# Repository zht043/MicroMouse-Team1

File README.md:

# MicroMouse-Team1

************************************************************************************************************************************

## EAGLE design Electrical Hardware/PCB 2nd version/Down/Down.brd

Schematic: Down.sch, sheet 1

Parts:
C1, C2: 12pF; 0603
CEM1, CEM3, CEM5, CEM7: 4.7µF; 0805
CEM2, CEM4, CEM6, CEM8: 0.1µF; 0805
CLMC_1: 0.1µF; 0805
CLMC_2: 100uF; EIA7343
CPWR_1, CPWR_5: 0.47µF; 0805
CPWR_2, CPWR_6: 22uF or 33uF; 0805
CPWR_3: 0.1uF; 0805
CPWR_4: 0.33µF; 0805
CRMC_1: 0.1µF; 0805
CRMC_2: 100uF; EIA7343
C_BAT: 2.2uF; 0805
C_V1, C_V2, C_V3, C_V4: 0.1uF; 0805
C_VA1: 2.2uF; 0805
C_VA2: 0.1uF; 0805
C_VCAP1, C_VCAP2: 2.2uF; 0805
IREL: JST-PH2
IRELF: JST-PH2
IRER: JST-PH2
IRERF: JST-PH2
IRRL: JST-PH2
IRRLF: JST-PH2
IRRR: JST-PH2
IRRRF: JST-PH2
LED1, LED2, LED3, LED4: BLUE; LED-1206
LEDR1, LEDR2, LEDR3, LEDR4: 1k; 0805
LEFTMOTOR: PINHD-2X3; 2X03
LM: 1X4
P1: JST-PH2
REG1, REG3: LM2940IMP-5.0/NOPB; MP04A
REG2: LM2937IMP-3.3/NOPB; MP04A
RIGHTMOTOR: PINHD-2X3; 2X03
RM: 1X4
RRE1, RRE2, RRE3, RRE4, RRE5, RRE6: 1.8k; 0805
R_EM, R_EM2, R_EM4, R_EM6: 5ohm; 0805
R_EM1, R_EM3, R_EM5, R_EM7: 10k; 0805
R_LMC_1, R_LMC_2: 47K; 0805
R_RMC_1, R_RMC_2: 47k; 0805
R_VMTR_1: 10K; 0805
R_VMTR_2: 20K; 0805
SPI2: 1X4
SWD: 1X5
U$1: STM32F405/415_LQFP64
U$2: OSC
U$3: 1X3
U$4, U$5, U$6, U$7: MCH3474
U$8, U$9: 1X2
U$15, U$17: TC4427(8MSOP)
U$16, U$18: ZXMHC3F381N8

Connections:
3.3V: CPWR_4.1, C_BAT.2, C_V1.2, C_V2.1, C_V3.2, C_V4.2, C_VA1.2, C_VA2.2, REG2.3 (OUT), SWD.5, U$1.VBAT, U$1.VDDA, U$1.VDD_0, U$1.VDD_1, U$1.VDD_2, U$1.VDD_3, U$3.2
5V: CPWR_3.1, CPWR_6.1, LEFTMOTOR.4, REG2.1 (IN), REG3.3 (VOUT), RIGHTMOTOR.4
A5V: CEM1.2, CEM2.1, CEM3.2, CEM4.1, CEM5.2, CEM6.1, CEM7.2, CEM8.1, CPWR_2.1, IREL.2, IRELF.2, IRER.2, IRERF.2, IRRL.2, IRRR.2, LEDR1.2, LEDR2.2, LEDR3.2, LEDR4.2, REG1.3 (VOUT)
AGND: CEM1.1, CEM2.2, CEM3.1, CEM4.2, CEM5.1, CEM6.2, CEM7.1, CEM8.2, CPWR_1.2, CPWR_2.2, LED1.C, LED2.C, LED3.C, LED4.C, REG1.2 (GND_2), REG1.4 (GND), RRE1.1, RRE2.1, RRE3.1, RRE4.1, RRE5.1, RRE6.1, R_EM1.1, R_EM3.1, R_EM5.1, R_EM7.1, R_VMTR_1.1, U$3.3, U$4.S, U$5.S, U$6.S, U$7.S
EMD_L: IREL.1, R_EM4.2
EMD_LF: IRELF.1, R_EM.2
EMD_R: IRER.1, R_EM6.2
EMD_RF: IRERF.1, R_EM2.2
EM_L: R_EM5.2, U$1.PA8, U$4.G
EM_LF: R_EM1.2, U$1.PA10, U$5.G
EM_R: R_EM7.2, U$1.PA9, U$7.G
EM_RF: R_EM3.2, U$1.PA11, U$6.G
GND: C1.2, C2.2, CPWR_3.2, CPWR_4.2, CPWR_5.2, CPWR_6.2, C_BAT.1, C_V1.1, C_V2.2, C_V3.1, C_V4.1, C_VA1.1, C_VA2.1, C_VCAP1.1, C_VCAP2.2, REG2.2 (GND), REG3.2 (GND_2), REG3.4 (GND), SWD.3, U$1.BOOT0, U$1.PB2, U$1.VSSA, U$1.VSS_0, U$1.VSS_1, U$3.1
L: LEFTMOTOR.1, U$16.N1D/P1D
LENCA: LEFTMOTOR.6, LM.1
LENCB: LEFTMOTOR.5, LM.2
LPWMA: LM.4, R_LMC_1.2, U$15.IN_A
LPWMB: LM.3, R_LMC_2.2, U$15.IN_B
MGND: CLMC_1.1, CLMC_2.C (-), CRMC_1.1, CRMC_2.C (-), LEFTMOTOR.3, P1.2, RIGHTMOTOR.3, R_LMC_1.1, R_LMC_2.1, R_RMC_1.1, R_RMC_2.1, U$15.GND, U$16.N1S/N2S, U$17.GND, U$18.N1S/N2S
unnamed: R_EM.1, U$5.D
unnamed: R_EM2.1, U$6.D
unnamed: R_EM4.1, U$4.D
unnamed: R_EM6.1, U$7.D
unnamed: LED2.A, LEDR1.1
unnamed: LED3.A, LEDR2.1
unnamed: LED4.A, LEDR3.1
unnamed: LED1.A, LEDR4.1
unnamed: LEFTMOTOR.2, U$16.N2D/P2D
unnamed: RIGHTMOTOR.1, U$18.N2D/P2D
OSC_IN: C1.1, U$1.PH0, U$2.P$2 (IN2)
OSC_OUT: C2.1, U$1.PH1, U$2.P$1 (IN1)
OUTA: U$17.OUT_A, U$18.N1G, U$18.P1G
OUTB: U$17.OUT_B, U$18.N2G, U$18.P2G
OUT_A: U$15.OUT_A, U$16.N1G, U$16.P1G
OUT_B: U$15.OUT_B, U$16.N2G, U$16.P2G
R: RIGHTMOTOR.2, U$18.N1D/P1D
RENCA: RIGHTMOTOR.6, RM.3
RENCB: RIGHTMOTOR.5, RM.4
RESET: SWD.1, U$1.NRST
RE_L: IRRL.1, RRE5.2, U$1.PA2
RE_LFA: IRRLF.2, RRE1.2, U$1.PC1
RE_LFB: IRRLF.1, RRE2.2, U$1.PC2
RE_R: IRRR.1, RRE6.2, U$1.PB0
RE_RFA: IRRRF.1, RRE3.2, U$1.PC4
RE_RFB: IRRRF.2, RRE4.2, U$1.PC5
RPWMA: RM.1, R_RMC_1.2, U$17.IN_B
RPWMB: RM.2, R_RMC_2.2, U$17.IN_A
SPI2_MISO: SPI2.3, U$1.PB14
SPI2_MOSI: SPI2.4, U$1.PB15
SPI2_NSS: SPI2.1, U$1.PB12
SPI2_SCK: SPI2.2, U$1.PB13
SWCLK: SWD.4, U$1.PA14
SWDIO: SWD.2, U$1.PA13
TAB1: REG2.4 (TAB)
VBAT: CLMC_1.2, CLMC_2.A (+), CPWR_1.1, CPWR_5.1, CRMC_1.2, CRMC_2.A (+), P1.1, REG1.1 (VIN), REG3.1 (VIN), R_VMTR_2.2, U$15.VDD, U$16.P1S/P2S, U$17.VDD, U$18.P1S/P2S
VCAP_1: C_VCAP1.2, U$1.VCAP_1
VCAP_2: C_VCAP2.1, U$1.VCAP_2
VMTR: R_VMTR_1.2, R_VMTR_2.1, U$1.PB1

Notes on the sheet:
Left Motor Controller
Right Motor Controller
Voltmeter

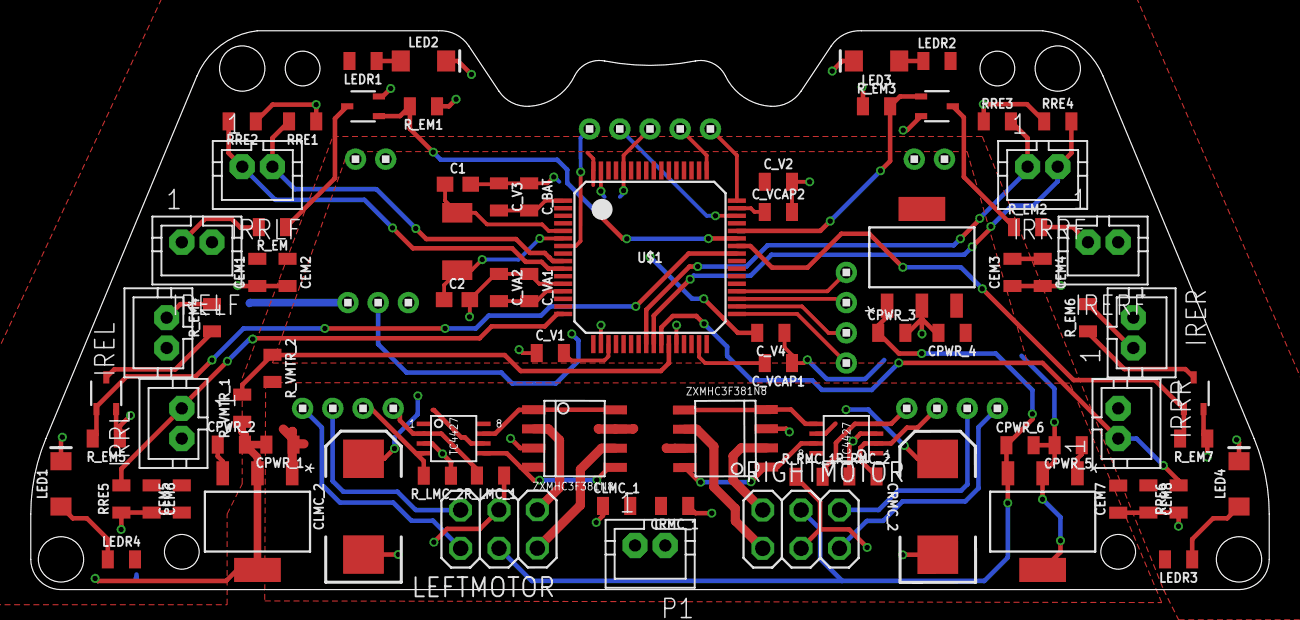
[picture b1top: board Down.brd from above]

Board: 2 copper layers, 82.0 x 37.0 mm, 88 parts (0 on the bottom side), 57 nets.

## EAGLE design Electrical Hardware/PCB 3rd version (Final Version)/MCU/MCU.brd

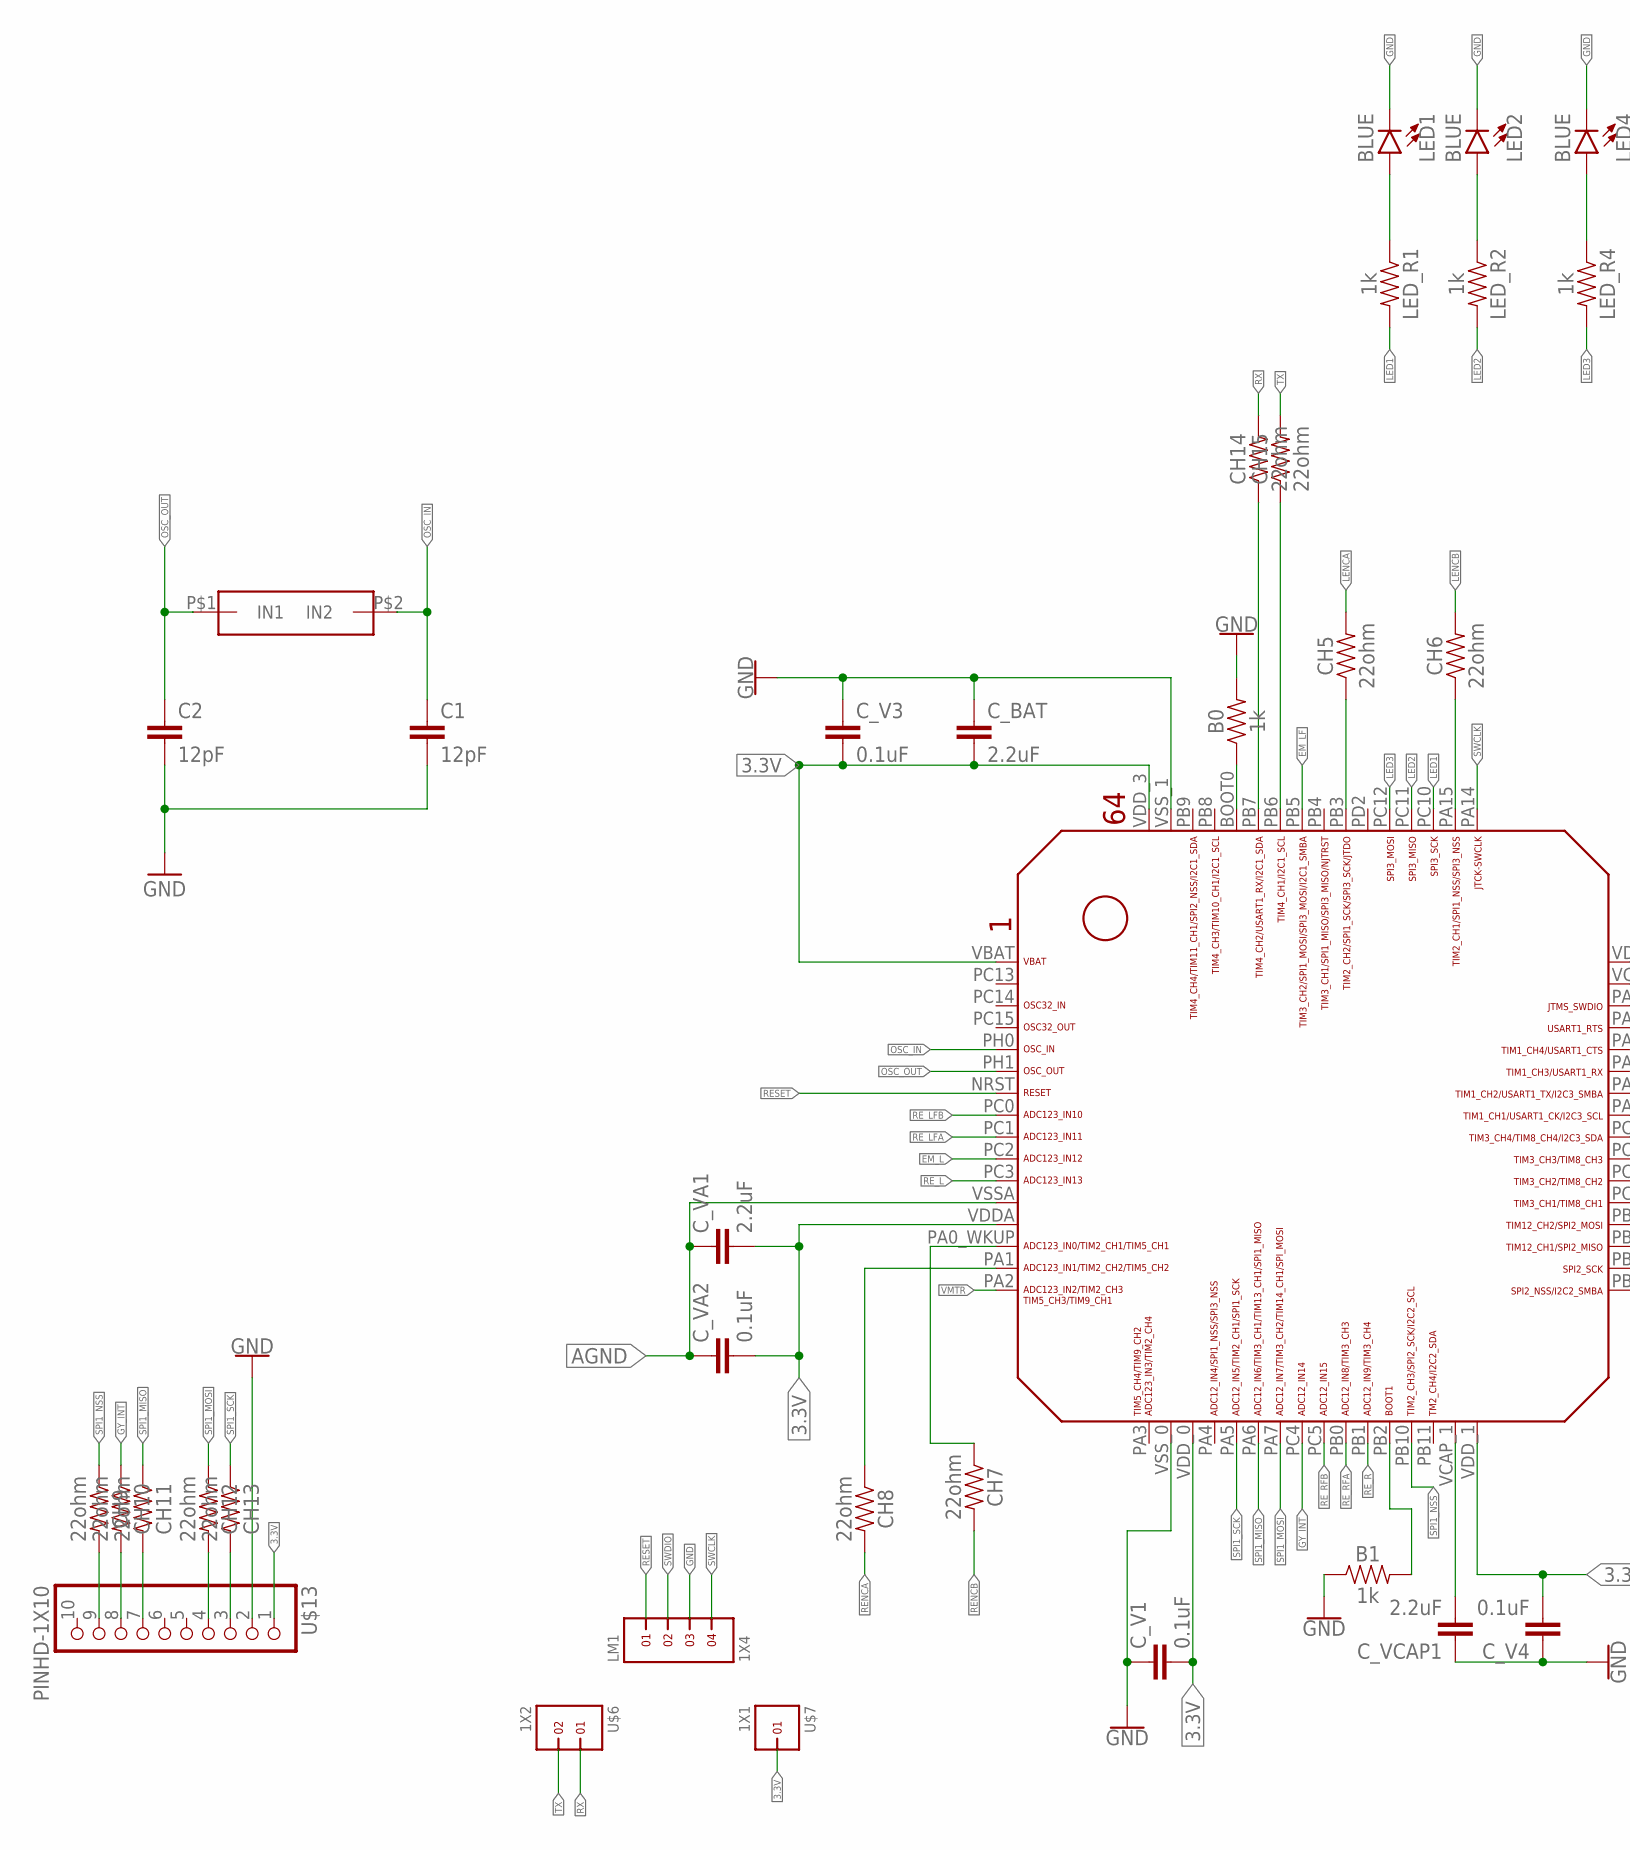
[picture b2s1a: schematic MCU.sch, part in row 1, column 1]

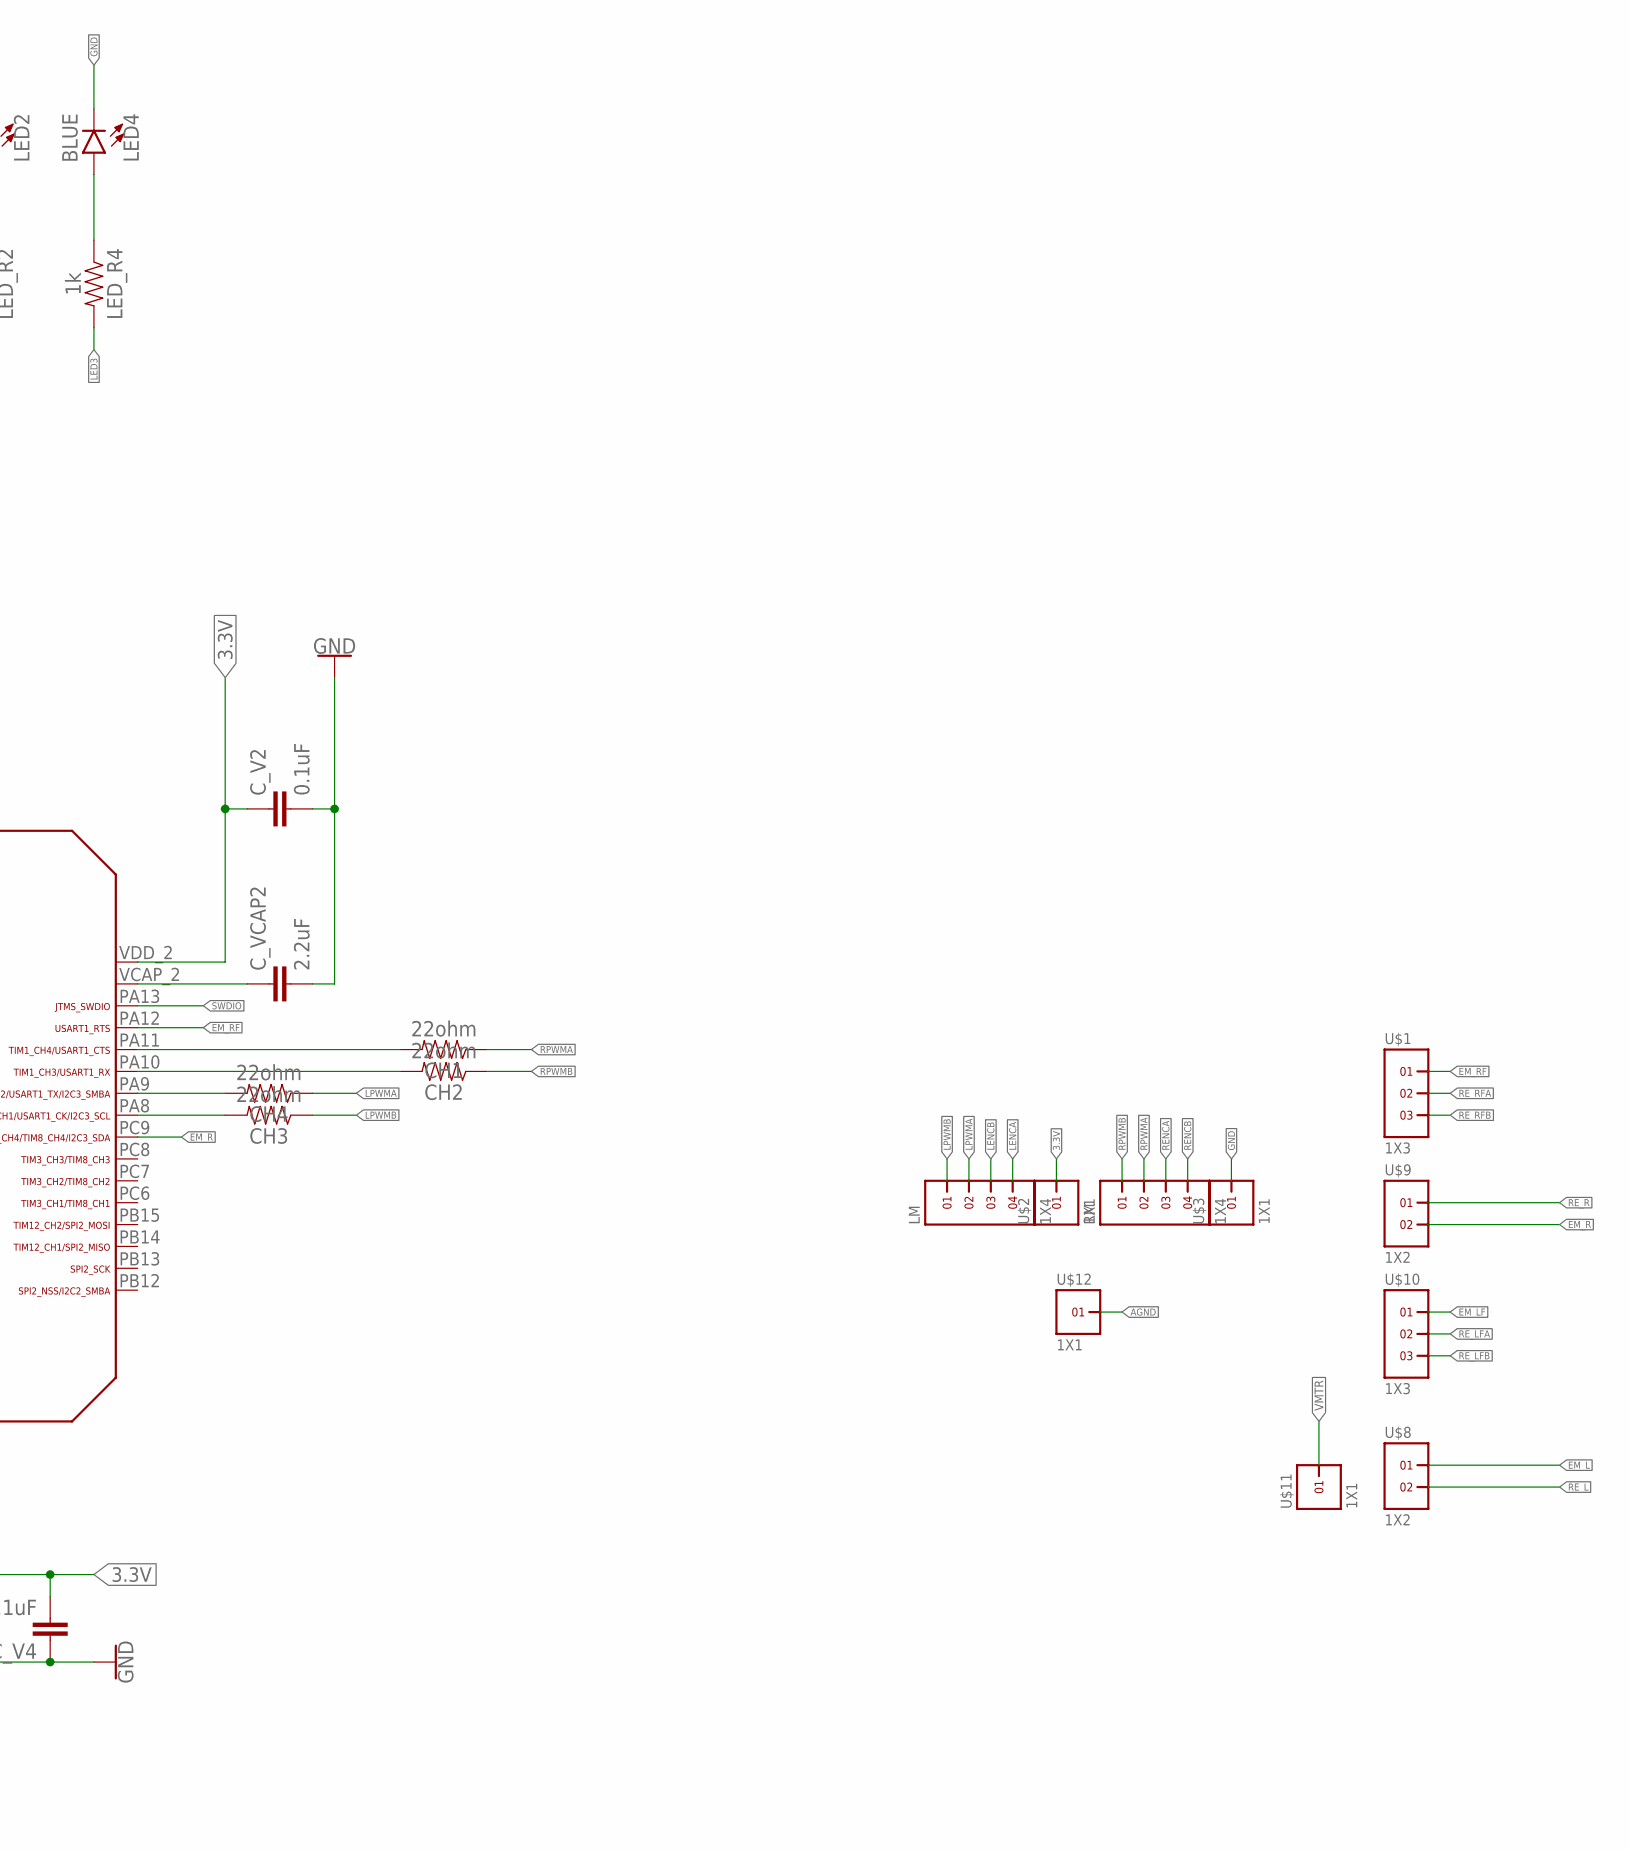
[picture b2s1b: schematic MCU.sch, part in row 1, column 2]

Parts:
B0, B1: 1k; 0805
C1, C2: 12pF; 0603
CH1, CH2, CH3, CH4, CH5, CH6, CH7, CH8, CH9, CH10, CH11, CH12, CH13, CH14, CH15: 22ohm; 0805
C_BAT: 2.2uF; 0805
C_V1, C_V2, C_V3, C_V4: 0.1uF; 0805
C_VA1: 2.2uF; 0805
C_VA2: 0.1uF; 0805
C_VCAP1, C_VCAP2: 2.2uF; 0805
LED1, LED2, LED4: BLUE; LED-1206
LED_R1, LED_R2, LED_R4: 1k; 0805
LM, LM1: 1X4
RM: 1X4
U$1, U$10: 1X3
U$2, U$3, U$7, U$11, U$12: 1X1
U$4: STM32F405/415_LQFP64
U$5: OSC
U$6, U$8, U$9: 1X2
U$13: PINHD-1X10; 1X10-BIG

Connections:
3.3V: C_BAT.2, C_V1.2, C_V2.1, C_V3.2, C_V4.2, C_VA1.2, C_VA2.2, U$2.1, U$4.VBAT, U$4.VDDA, U$4.VDD_0, U$4.VDD_1, U$4.VDD_2, U$4.VDD_3, U$7.1, U$13.1; also elsewhere on the board
AGND: C_VA1.1, C_VA2.1, U$4.VSSA, U$12.1
EM_L: U$4.PC2, U$8.1
EM_LF: U$4.PB5, U$10.1
EM_R: U$4.PC9, U$9.2
EM_RF: U$1.1, U$4.PA12
GND: B0.2, B1.1, C1.2, C2.2, C_BAT.1, C_V1.1, C_V2.2, C_V3.1, C_V4.1, C_VCAP1.1, C_VCAP2.2, LED1.C, LED2.C, LED4.C, LM1.3, U$3.1, U$4.VSS_0, U$4.VSS_1, U$13.2; also elsewhere on the board
GY_INT: CH10.1, U$4.PC4
INT: CH10.2, U$13.8
LED1: LED_R1.2, U$4.PC10
LED2: LED_R2.2, U$4.PC11, U$4.PC15
LENCA: CH5.2, LM.4
LENCB: CH6.2, LM.3
LPWMA: CH4.1, LM.2
LPWMB: CH3.1, LM.1
MISO: CH11.2, U$13.7
MOSI: CH12.2, U$13.4
unnamed: CH3.2, U$4.PA8
unnamed: CH4.2, U$4.PA9
unnamed: CH1.2, U$4.PA11
unnamed: CH2.2, U$4.PA10
unnamed: CH6.1, U$4.PA15
unnamed: CH5.1, U$4.PB3
unnamed: CH7.1, U$4.PA0_WKUP (PA0_AKUP)
unnamed: CH8.1, U$4.PA1
unnamed: B1.2, U$4.PB2
unnamed: B0.1, U$4.BOOT0
unnamed: CH14.1, U$4.PB7
unnamed: CH15.1, U$4.PB6
unnamed: LED2.A, LED_R2.1
unnamed: LED1.A, LED_R1.1
NSS: CH9.2, U$13.9
unnamed: LED4.A, LED_R4.1
unnamed: LED_R4.2, U$4.PC12
OSC_IN: C1.1, U$4.PH0, U$5.P$2 (IN2)
OSC_OUT: C2.1, U$4.PH1, U$5.P$1 (IN1)
RENCA: CH8.2, RM.3
RENCB: CH7.2, RM.4
RESET: LM1.1, U$4.NRST; also elsewhere on the board
RE_L: U$4.PC3, U$8.2
RE_LFA: U$4.PC1, U$10.2
RE_LFB: U$4.PC0, U$10.3
RE_R: U$4.PB1, U$9.1
RE_RFA: U$1.2, U$4.PB0
RE_RFB: U$1.3, U$4.PC5
RPWMA: CH1.1, RM.2
RPWMB: CH2.1, RM.1
RX: CH14.2, U$6.1
SCK: CH13.2, U$13.3
SPI1_MISO: CH11.1, U$4.PA6
SPI1_MOSI: CH12.1, U$4.PA7
SPI1_NSS: CH9.1, U$4.PB10
SPI1_SCK: CH13.1, U$4.PA5
SWCLK: LM1.4, U$4.PA14
SWDIO: LM1.2, U$4.PA13
TX: CH15.2, U$6.2
VCAP_1: C_VCAP1.2, U$4.VCAP_1
VCAP_2: C_VCAP2.1, U$4.VCAP_2
VMTR: U$4.PA2, U$11.1

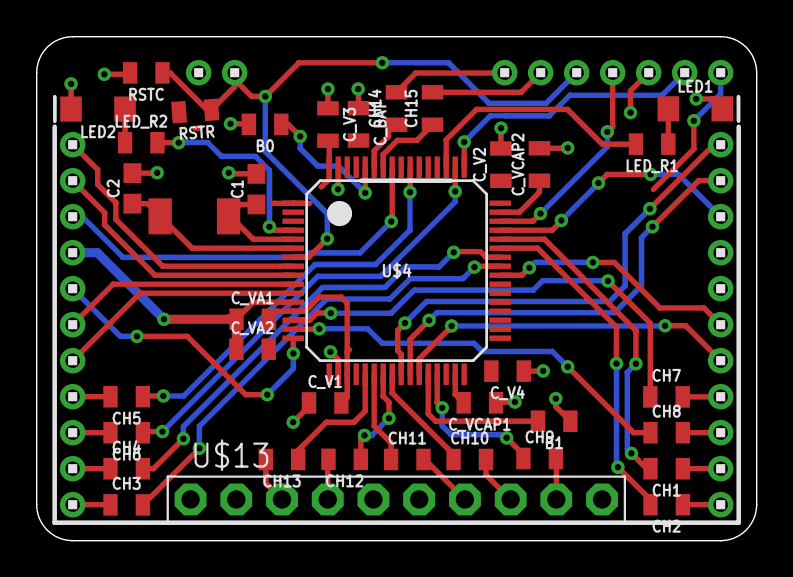
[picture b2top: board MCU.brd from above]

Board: 2 copper layers, 40.0 x 28.0 mm, 51 parts (0 on the bottom side), 57 nets.

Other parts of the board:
BUTTON: 1X2
RSTC: 0.1uf; 0805
RSTR: 47K; 0805

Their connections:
3.3V: RSTR.2; also elsewhere on the board
GND: BUTTON.1, RSTC.2; also elsewhere on the board
RESET: BUTTON.2, RSTC.1, RSTR.1; also elsewhere on the board

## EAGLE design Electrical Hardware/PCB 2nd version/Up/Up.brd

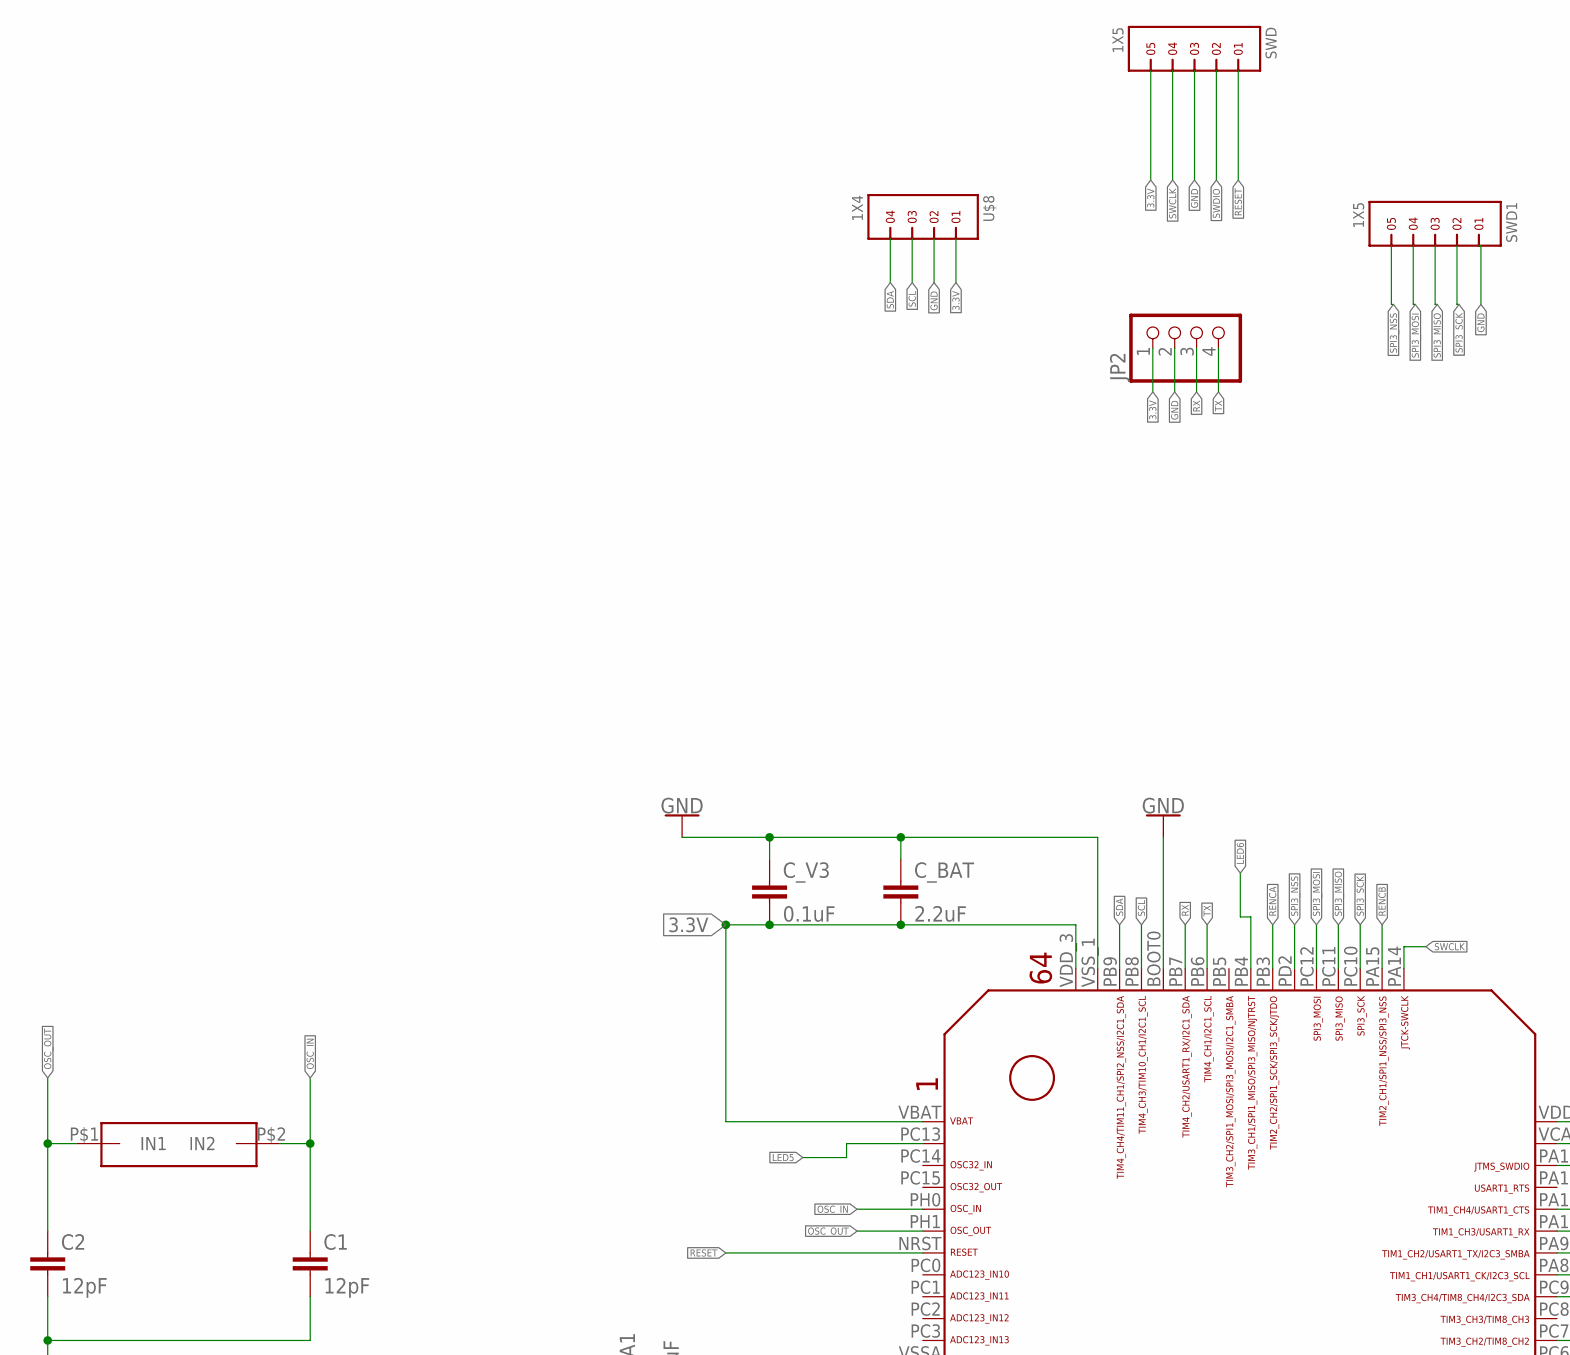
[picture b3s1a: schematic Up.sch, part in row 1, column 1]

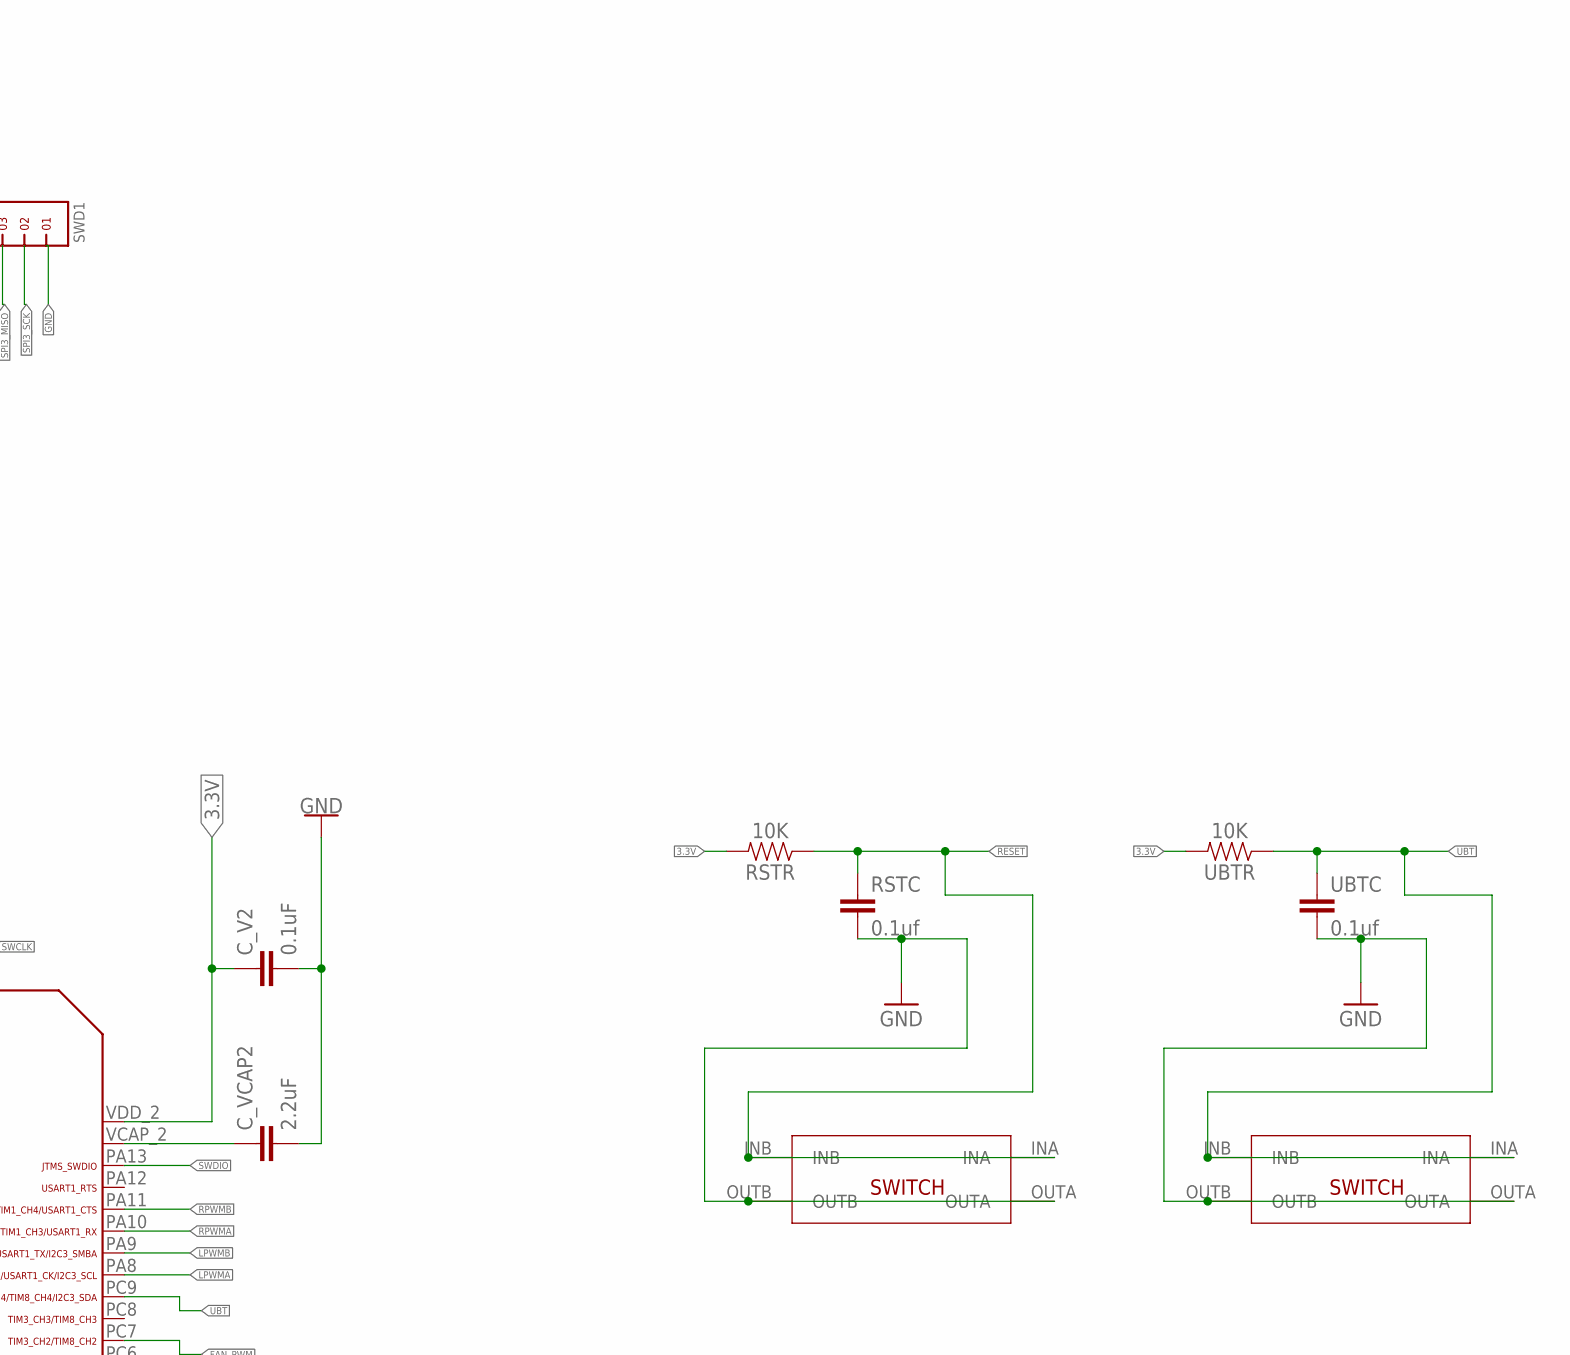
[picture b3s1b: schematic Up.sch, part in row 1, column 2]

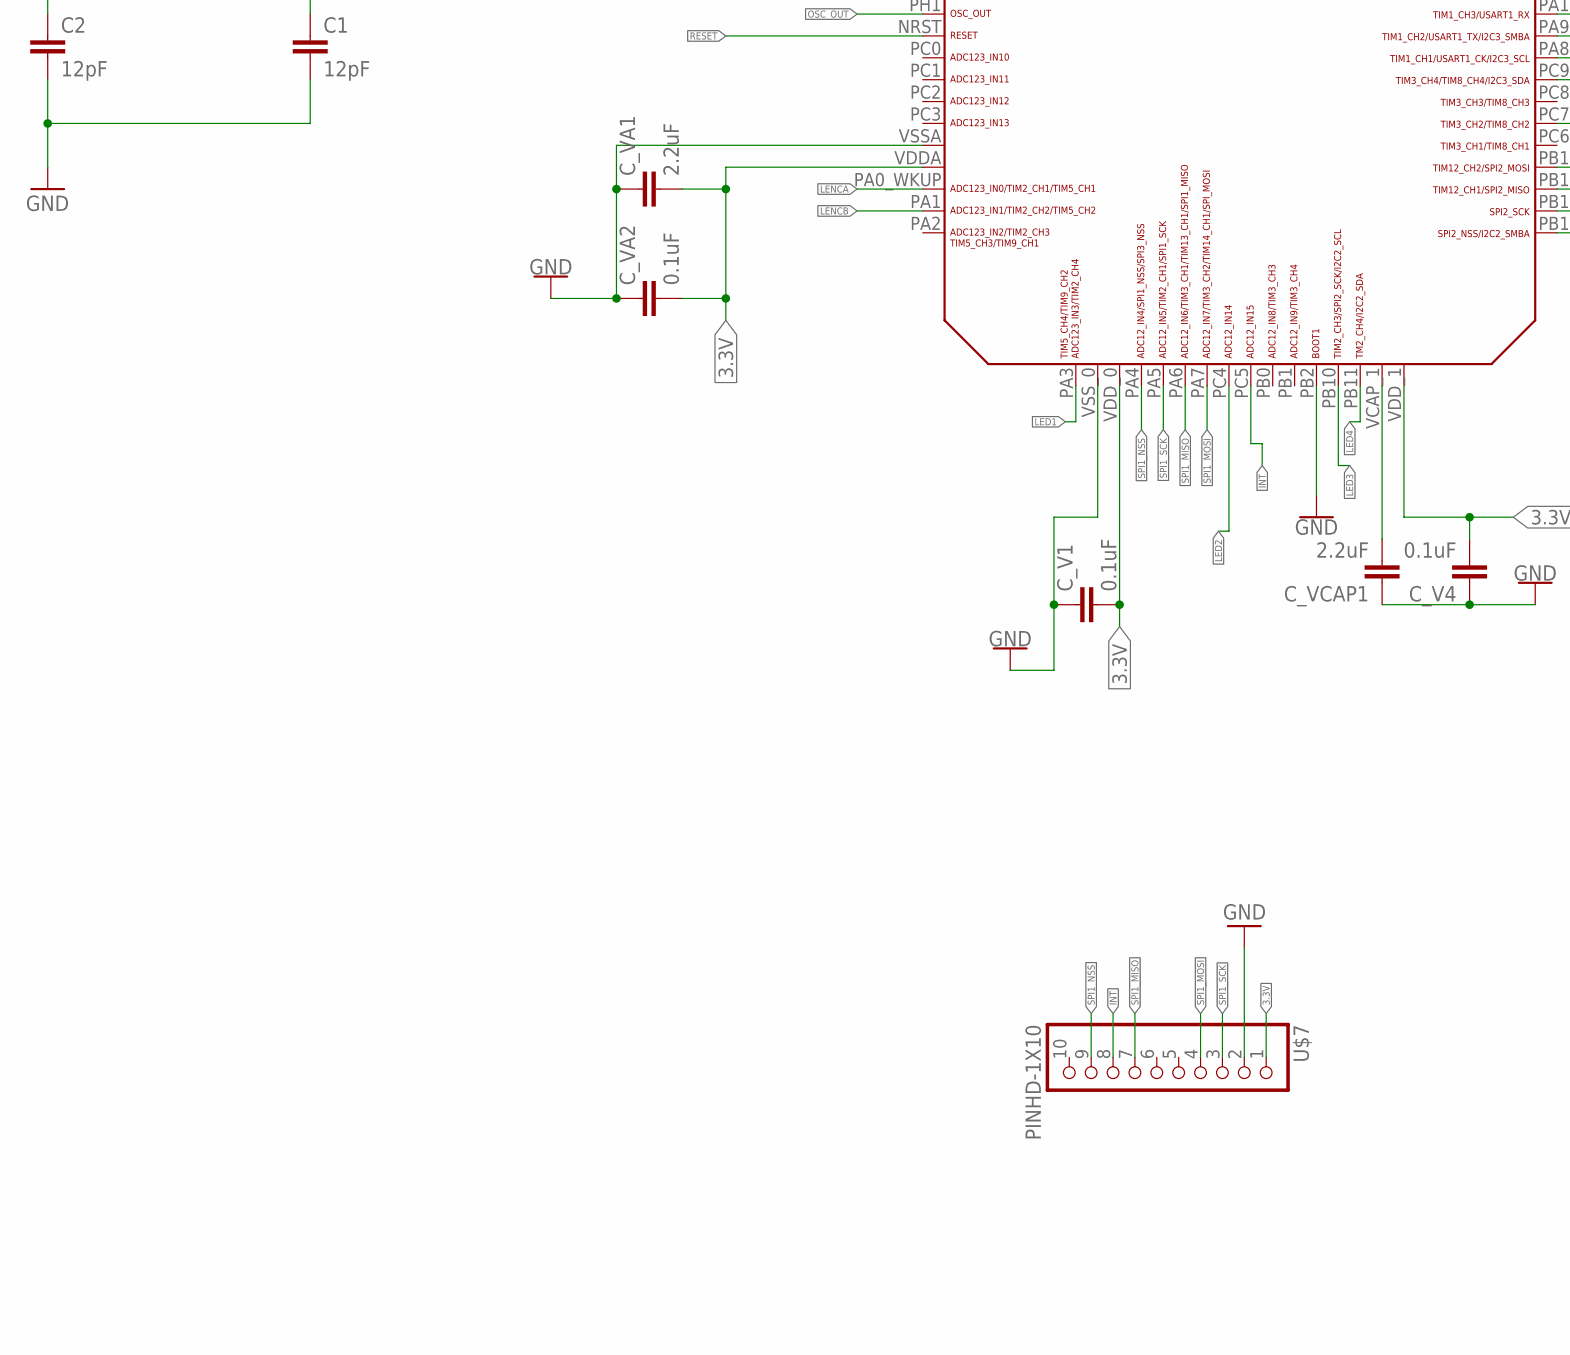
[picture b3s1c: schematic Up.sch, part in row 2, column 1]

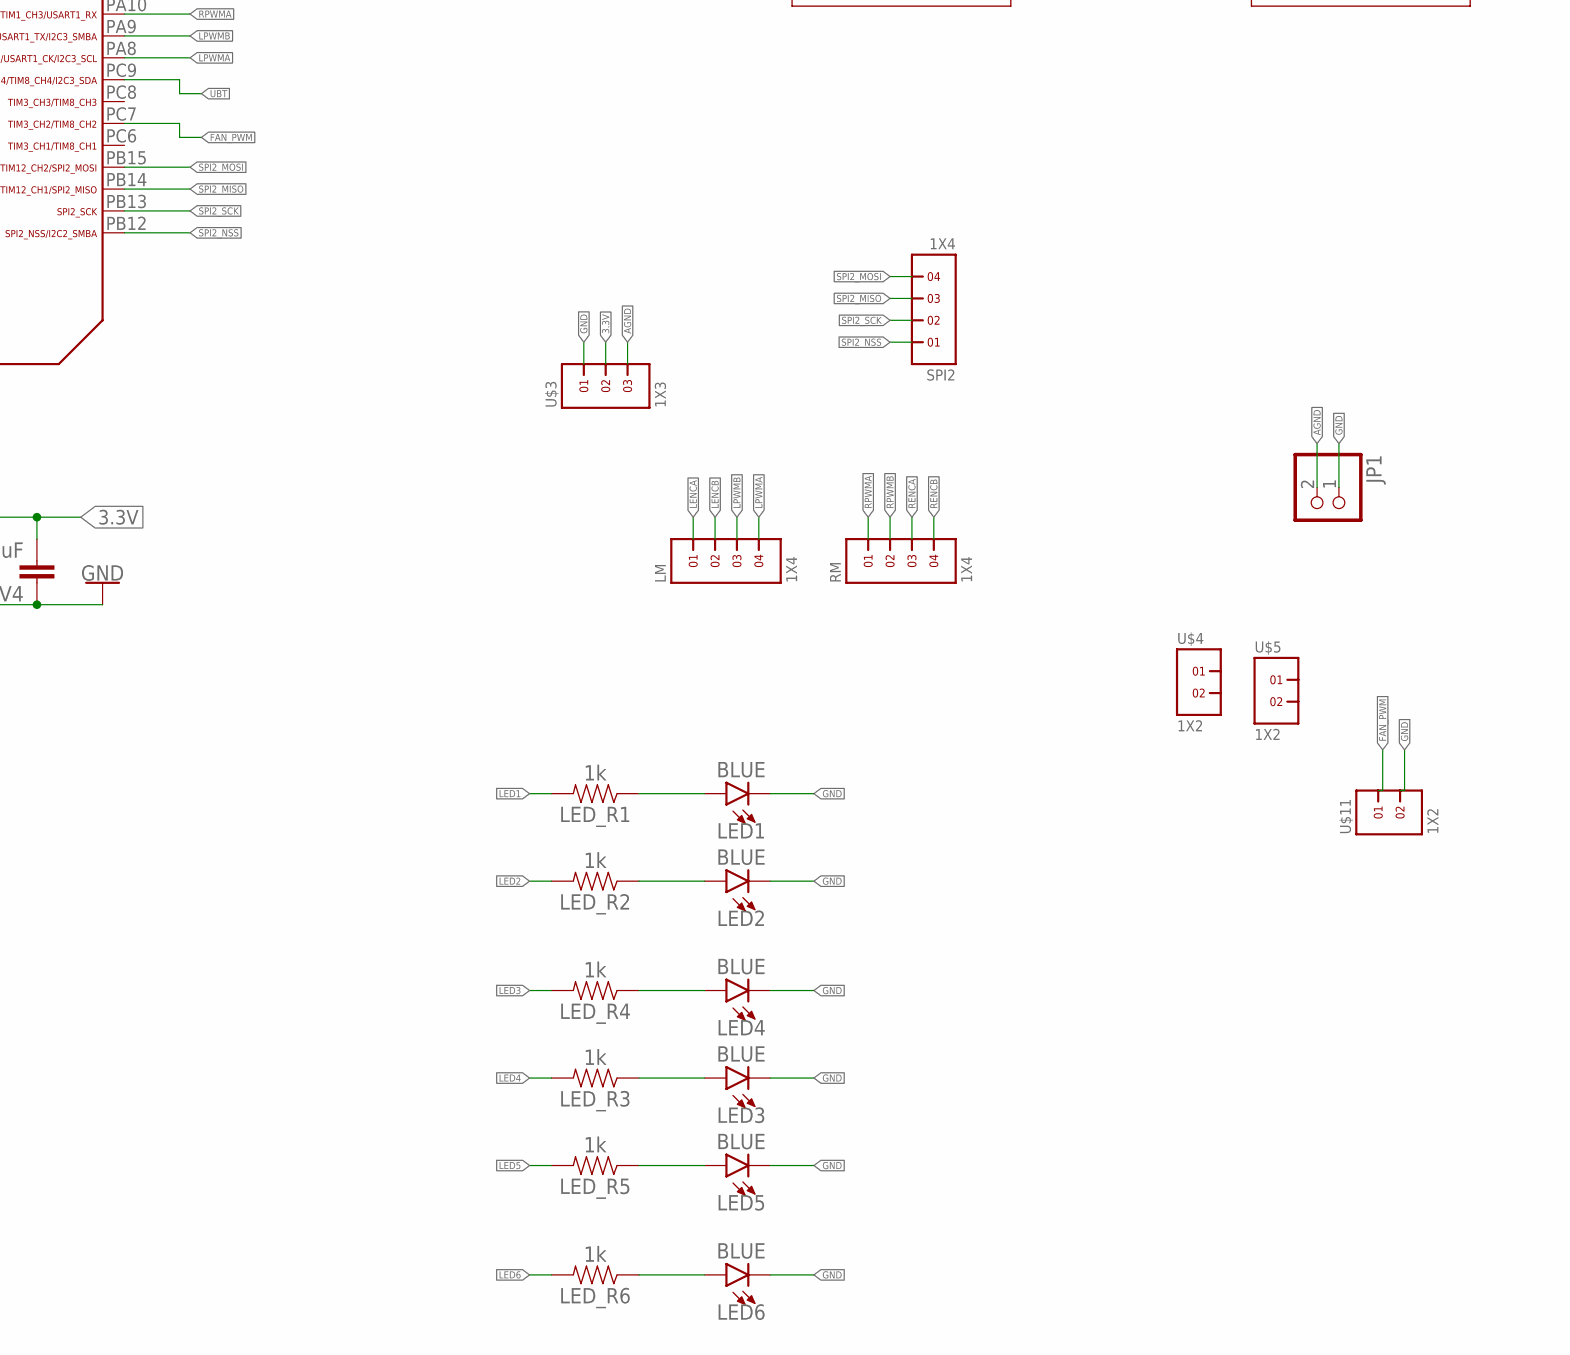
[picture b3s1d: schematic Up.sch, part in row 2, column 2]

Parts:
C1, C2: 12pF; 0603
CX5032GA*8MHZ*CYSTAL: OSC
C_BAT: 2.2uF; 0805
C_V1, C_V2, C_V3, C_V4: 0.1uF; 0805
C_VA1: 2.2uF; 0805
C_VA2: 0.1uF; 0805
C_VCAP1, C_VCAP2: 2.2uF; 0805
JP1: PINHD-1X2; 1X02
JP2: PINHD-1X4; 1X04
LED1, LED2, LED3, LED4, LED5, LED6: BLUE; LED-1206
LED_R1, LED_R2, LED_R3, LED_R4, LED_R5, LED_R6: 1k; 0805
LM: 1X4
RM: 1X4
RSTC: 0.1uf; 0805
RSTR: 10K; 0805
SPI2: 1X4
SWD, SWD1: 1X5
U$1: STM32F405/415_LQFP64
U$3: 1X3
U$4, U$5, U$11: 1X2
U$7: PINHD-1X10; 1X10-BIG
U$8: 1X4
U$9, U$10: 4X4X1.5_SMD_SWITCH
UBTC: 0.1uf; 0805
UBTR: 10K; 0805

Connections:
3.3V: C_BAT.2, C_V1.2, C_V2.1, C_V3.2, C_V4.2, C_VA1.2, C_VA2.2, JP2.1, RSTR.2, SWD.5, U$1.VBAT, U$1.VDDA, U$1.VDD_0, U$1.VDD_1, U$1.VDD_2, U$1.VDD_3, U$3.2, U$7.1, U$8.1, UBTR.2
AGND: JP1.2, U$3.3
FAN_PWM: U$1.PC7, U$11.1
GND: C1.2, C2.2, C_BAT.1, C_V1.1, C_V2.2, C_V3.1, C_V4.1, C_VA1.1, C_VA2.1, C_VCAP1.1, C_VCAP2.2, JP1.1, JP2.2, LED1.C, LED2.C, LED3.C, LED4.C, LED5.C, LED6.C, RSTC.2, SWD.3, SWD1.1, U$1.BOOT0, U$1.PB2, U$1.VSSA, U$1.VSS_0, U$1.VSS_1, U$3.1, U$7.2, U$8.2, U$9.OUTA, U$9.OUTB, U$10.OUTA, U$10.OUTB, U$11.2, UBTC.2
INT: U$1.PC5, U$7.8
LED1: LED_R1.2, U$1.PA3
LED2: LED_R2.2, U$1.PC4
LED3: LED_R4.2, U$1.PB10
LED4: LED_R3.2, U$1.PB11
LED5: LED_R5.2, U$1.PC13
LED6: LED_R6.2, U$1.PB4
LENCA: LM.1, U$1.PA0_WKUP (PA0_AKUP)
LENCB: LM.2, U$1.PA1
LPWMA: LM.4, U$1.PA8
LPWMB: LM.3, U$1.PA9
unnamed: LED3.A, LED_R3.1
unnamed: LED4.A, LED_R4.1
unnamed: LED5.A, LED_R5.1
unnamed: LED6.A, LED_R6.1
unnamed: LED2.A, LED_R2.1
unnamed: LED1.A, LED_R1.1
OSC_IN: C1.1, CX5032GA*8MHZ*CYSTAL.P$2 (IN2), U$1.PH0; also elsewhere on the board
OSC_OUT: C2.1, CX5032GA*8MHZ*CYSTAL.P$1 (IN1), U$1.PH1; also elsewhere on the board
RENCA: RM.3, U$1.PB3
RENCB: RM.4, U$1.PA15
RESET: RSTC.1, RSTR.1, SWD.1, U$1.NRST, U$9.INA, U$9.INB
RPWMA: RM.1, U$1.PA10
RPWMB: RM.2, U$1.PA11
RX: JP2.3, U$1.PB7
SCL: U$1.PB8, U$8.3
SDA: U$1.PB9, U$8.4
SPI1_MISO: U$1.PA6, U$7.7
SPI1_MOSI: U$1.PA7, U$7.4
SPI1_NSS: U$1.PA4, U$7.9
SPI1_SCK: U$1.PA5, U$7.3
SPI2_MISO: SPI2.3, U$1.PB14
SPI2_MOSI: SPI2.4, U$1.PB15
SPI2_NSS: SPI2.1, U$1.PB12
SPI2_SCK: SPI2.2, U$1.PB13
SPI3_MISO: SWD1.3, U$1.PC11
SPI3_MOSI: SWD1.4, U$1.PC12
SPI3_NSS: SWD1.5, U$1.PD2
SPI3_SCK: SWD1.2, U$1.PC10
SWCLK: SWD.4, U$1.PA14
SWDIO: SWD.2, U$1.PA13
TX: JP2.4, U$1.PB6
UBT: U$1.PC9, U$10.INA, U$10.INB, UBTC.1, UBTR.1
VCAP_1: C_VCAP1.2, U$1.VCAP_1
VCAP_2: C_VCAP2.1, U$1.VCAP_2

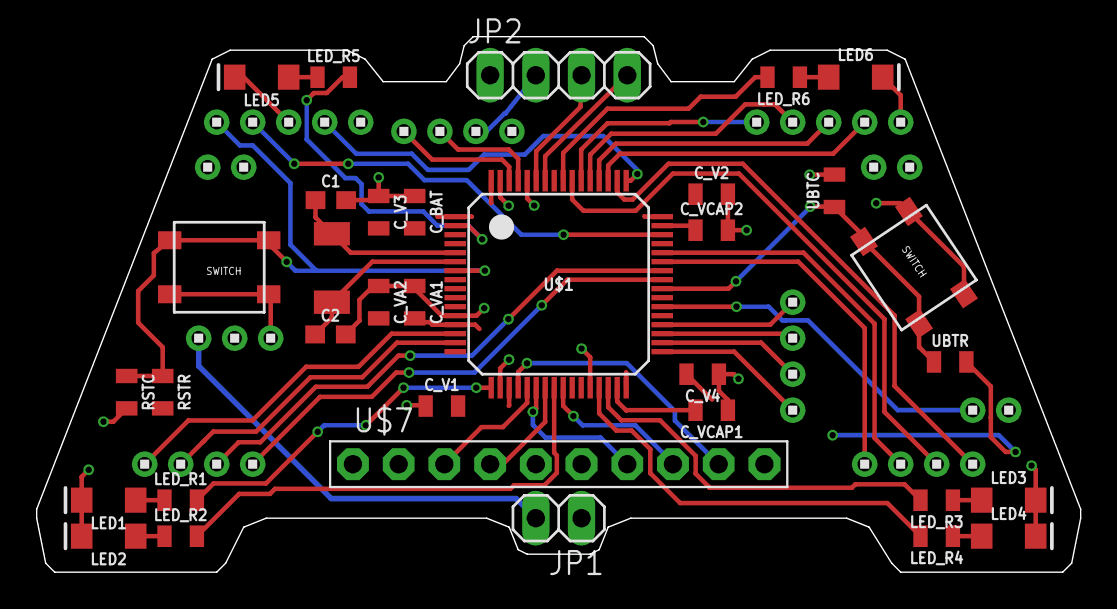
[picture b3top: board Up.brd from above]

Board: 2 copper layers, 58.0 x 29.8 mm, 44 parts (0 on the bottom side), 49 nets.

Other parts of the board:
CX5032GA: OSC

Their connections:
OSC_IN: CX5032GA.P$2; also elsewhere on the board
OSC_OUT: CX5032GA.P$1; also elsewhere on the board

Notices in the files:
parts and their libraries:
SparkFun-Capacitors: Licensing: Creative Commons ShareAlike 4.0 International - https://creativecommons.org/licenses/by-sa/4.0
COPYRIGHT: Copyright C 2015 Accelerated Designs. All rights reserved
